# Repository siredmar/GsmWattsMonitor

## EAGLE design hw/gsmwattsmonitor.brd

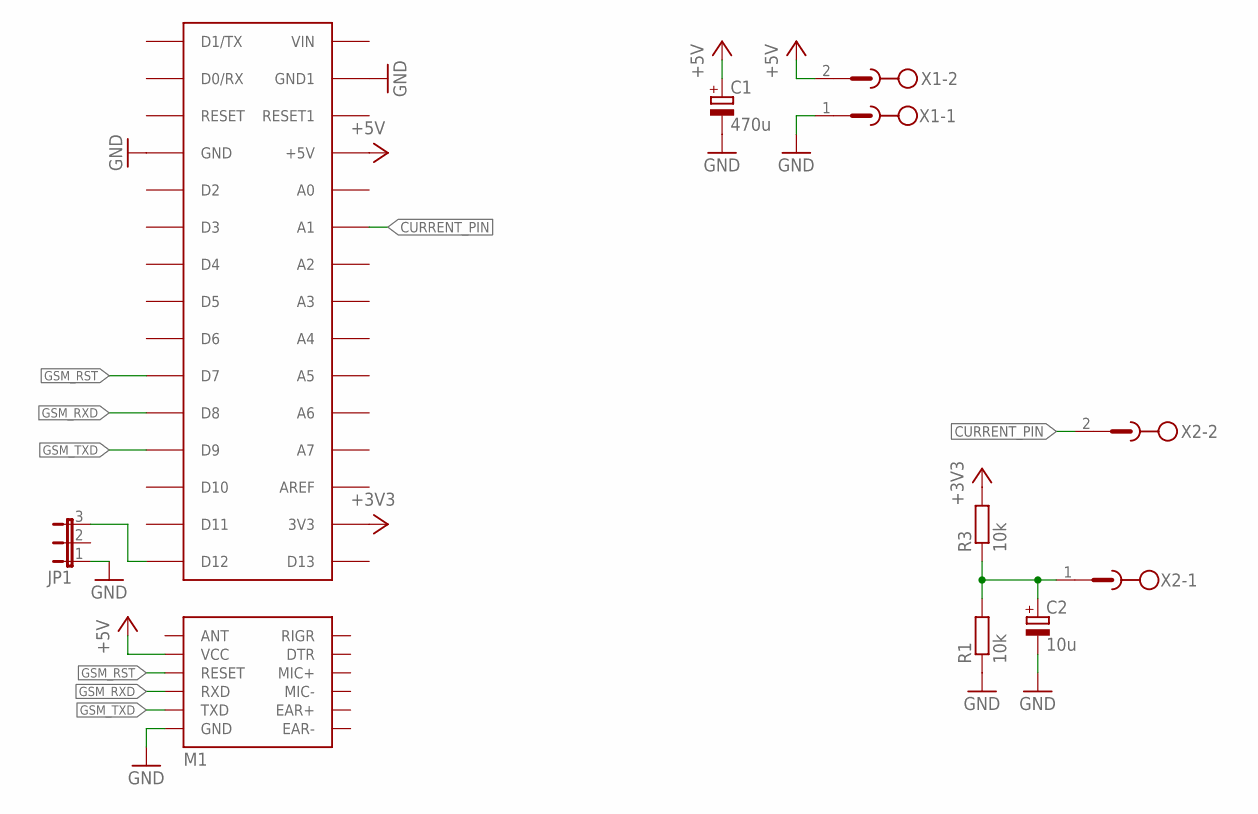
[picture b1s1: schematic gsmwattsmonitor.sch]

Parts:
C1: 470u; E2,5-6
C2: 10u; E2-4
JP1: JP2E; JP2
M1: SIM800L
R1, R3: 10k; 0204/7
U$1: ARDUINONANO; PDIP-32
X1, X2: MSTBV2

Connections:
+3V3: R3.2, U$1.3V3
+5V: C1.+, M1.VCC, U$1.+5V, X1.2
CURRENT_PIN: U$1.A1, X2.2
GND: C1.-, C2.-, JP1.1, M1.GND, R1.1, U$1.GND, U$1.GND1, X1.1
GSM_RST: M1.RESET, U$1.D7
GSM_RXD: M1.RXD, U$1.D8
GSM_TXD: M1.TXD, U$1.D9
unnamed: C2.+, R1.2, R3.1, X2.1
unnamed: JP1.3, U$1.D12

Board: 2 copper layers, 9 parts (0 on the bottom side), 9 nets, no tracks yet.

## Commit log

2018-09-16 Added current project state
2018-09-16 added text change
2018-09-16 Improved SIM Pin handling
2018-09-16 added EmonLib to project
2018-09-16 Added initial handling of emon sensor
2018-09-16 Calibration tests
2018-09-16 Added sensor docu
2018-09-16 Added commands for configuring trigger
2018-09-17 Addd moving average library
2018-09-18 Added trigger switch and further commands
2018-09-18 reordered commands in help, removed internet related gsm stuff
2018-09-20 Final hw related adjustments, added signaling LED
2018-09-22 Added trigger switch status
2018-09-22 updated hardware
2018-09-22 Fixed bugs related trigger
2018-09-24 Sim800 library modifications
2018-09-24 String to const String&
2018-09-24 Missing modifications after merge
2018-09-24 Sim handling improved
2018-09-25 Enabled fast blinking again
2020-03-22 Verbose improvements
